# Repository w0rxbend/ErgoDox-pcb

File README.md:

# ErgoDox RP2040

An ErgoDox split keyboard PCB rebuilt around an RP2040 in each half, with ZMK firmware, USB-C on every port and one RGB LED per key. It keeps the original ErgoDox switch positions, so it fits the Litster acrylic case.

**Status: in development. The boards are not finished and have never been fabricated. Do not order them yet.** See [PLAN.md](PLAN.md) for what is open.

Project page: <https://w0rxbend.github.io/ErgoDox-pcb/>

Front, left and right half. The switches plug in from this side. The small squares are the LED cutouts.

Back, seen from behind, so the right half is on the left. Sockets, diodes, LEDs and the controller are all here.

These are KiCad 3D renders of the current placement. The signal tracks are not routed yet, and the USB-C receptacles and buttons have no 3D model, so only their pads show on the front.

## What it is

| | Original ErgoDox (2016) | ErgoDox RP2040 |
| --- | --- | --- |
| Controller | Teensy 2.0 plus MCP23018 expander | One RP2040 per half |
| Firmware | QMK and others | ZMK, wired split |
| Computer port | Mini-USB | USB-C |
| Link between halves | TRRS, I2C | USB-C cable carrying UART |
| Master half | Fixed (the Teensy side) | Either half |
| Switches | Soldered | Hotswap sockets |
| Lighting | 3 indicator LEDs | One SK6812MINI-E per key |
| Board | One reversible 2-layer PCB | Separate left and right 4-layer PCBs |
| Keys | 38 per half | 38 per half |

### Either half can be the master

Both halves carry the same circuit. ZMK fixes the role at build time, so there are four firmware images: left or right, central or peripheral. Flash the central image into the half you plug into the computer and the peripheral image into the other half. To swap sides, reflash both halves over USB.

The link port is a USB-C receptacle, but it carries UART and 5 V, not USB. It is marked `LINK` and `NOT A PC PORT` on the board.

## Repository layout

| Path | Contents |
| --- | --- |
| `hw/ergodox-rp2040/DESIGN.md` | The design contract: circuit, pin map, parts, acceptance checks |
| `hw/ergodox-rp2040/left`, `right` | Generated KiCad 10 projects |
| `hw/ergodox-rp2040/tools` | Python scripts that generate the schematics and boards |
| `hw/ergodox-rp2040/firmware/zmk` | ZMK shield, as a Zephyr module |
| `hw/ergodox-rp2040/notes` | Geometry taken from the legacy board, part research, ZMK notes |
| `hw/ergodox-rp2040/third_party/MX_V2` | ai03 keyswitch footprint library |
| `docs` | Source of the project page |
| `ErgoDOX pcb` | The original 2016 KiCad board. Kept unchanged for reference |
| `ErgoDox Acrylic Case` | Litster acrylic case drawings. Kept unchanged |

## Rebuild the boards

The KiCad files are generated. Do not edit them by hand; change the scripts and run them again.

You need Docker and the `kicad/kicad:10.0.7-full` image.

From the repository root:

```sh
hw/ergodox-rp2040/tools/build.sh
```

The script runs these steps for both halves:

1. `build_board.py` writes the schematics and places every part.
2. `kicad-cli pcb drc` lists the open connections.
3. `finish.py` routes them. It is a grid router written for this board: 0.1 mm signal tracks, 0.4 mm power tracks and 0.2907 mm USB tracks, on the outer layers and on In2 round the controller. This takes one to three hours per half.
4. `kicad-cli pcb drc` fills the zones and writes the reports to `hw/ergodox-rp2040/reports`.

Write the JLCPCB files (Gerber zip, BOM and CPL) to `hw/ergodox-rp2040/fab` with:

```sh
hw/ergodox-rp2040/tools/export_fab.sh
```

Render the boards again after a change:

```sh
docker run --rm --user "$(id -u):$(id -g)" -e HOME=/tmp -v "$PWD":/work -w /work/hw/ergodox-rp2040 \
  kicad/kicad:10.0.7-full kicad-cli pcb render --side top --background transparent \
  -o /work/right-front.png right/ergodox-rp2040-right.kicad_pcb
```

Use `--side bottom` for the back. The README images are the left and right renders joined side by side.

Check the firmware pin map against the schematics with:

```sh
python3 hw/ergodox-rp2040/tools/check_firmware_pins.py
```

## Firmware

The ZMK shield is in `hw/ergodox-rp2040/firmware/zmk`. Add that directory to your ZMK build as an extra module and build these shields for the `rpi_pico` board:

- `ergodox_rp2040_left_central`
- `ergodox_rp2040_left_peripheral`
- `ergodox_rp2040_right_central`
- `ergodox_rp2040_right_peripheral`

The firmware has not been built or run on hardware yet. LED brightness is capped at 10% so both halves stay within 500 mA from one USB port.

## Known limits

- ZMK's wired split is new and has no runtime role switch. The role follows the flashed image.
- The RP2040 drives the LED data line at 3.3 V with no level shifter. This is outside the LED's guaranteed input level at 5 V.
- The USB-C openings have not been test fitted in the Litster case.
- Some resistor values have no verified JLCPCB part number yet. `DESIGN.md` lists them.

## Credits

Based on the open [ErgoDox](https://github.com/Ergodox-io/ErgoDox) PCB and the acrylic case designed by Litster. Keyswitch footprints are from ai03's MX_V2 library.

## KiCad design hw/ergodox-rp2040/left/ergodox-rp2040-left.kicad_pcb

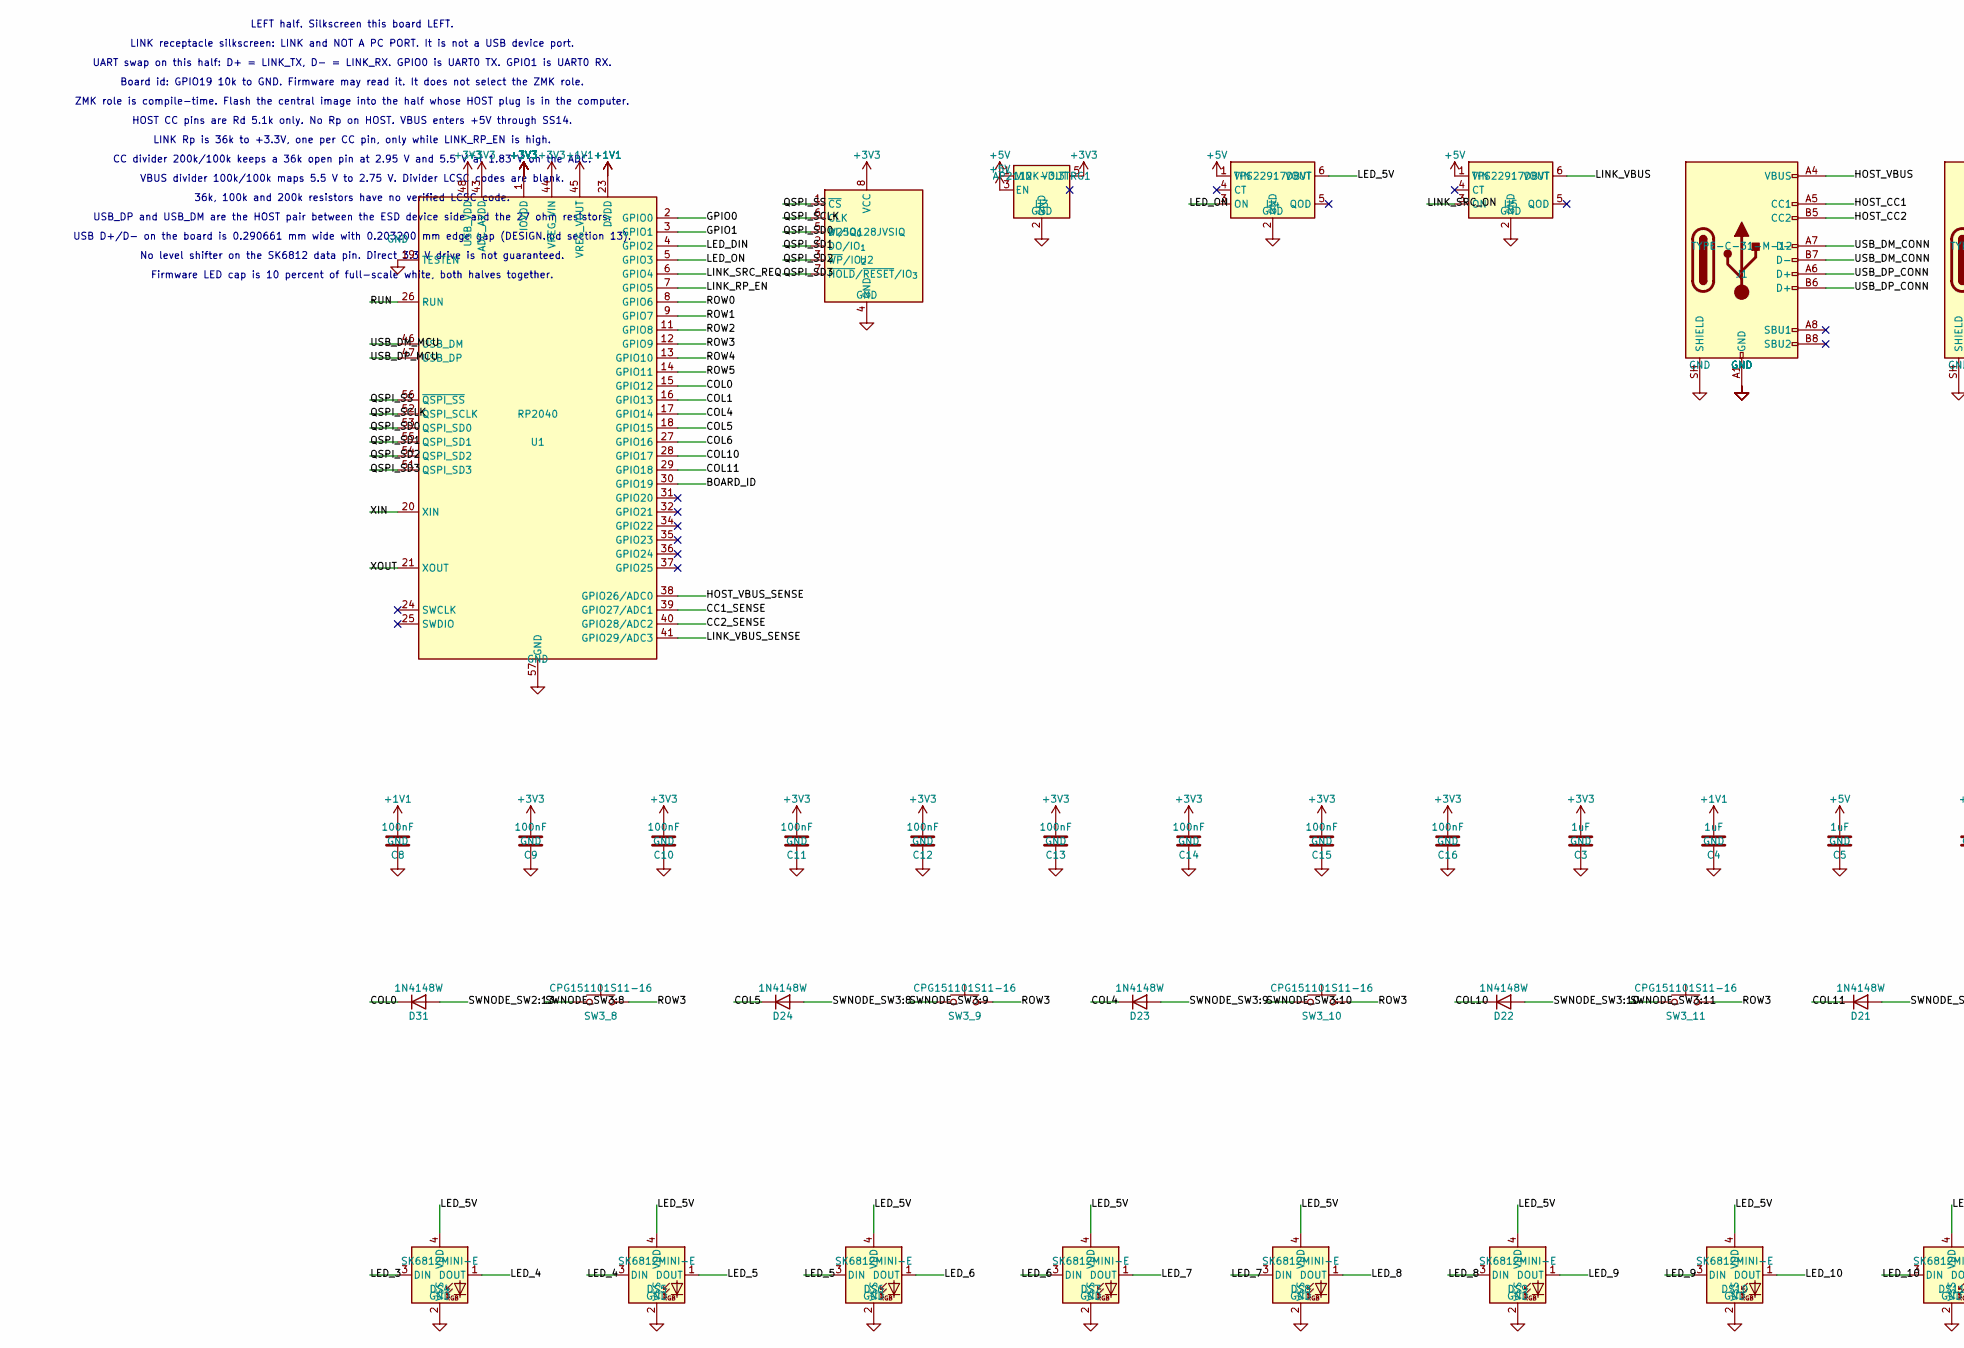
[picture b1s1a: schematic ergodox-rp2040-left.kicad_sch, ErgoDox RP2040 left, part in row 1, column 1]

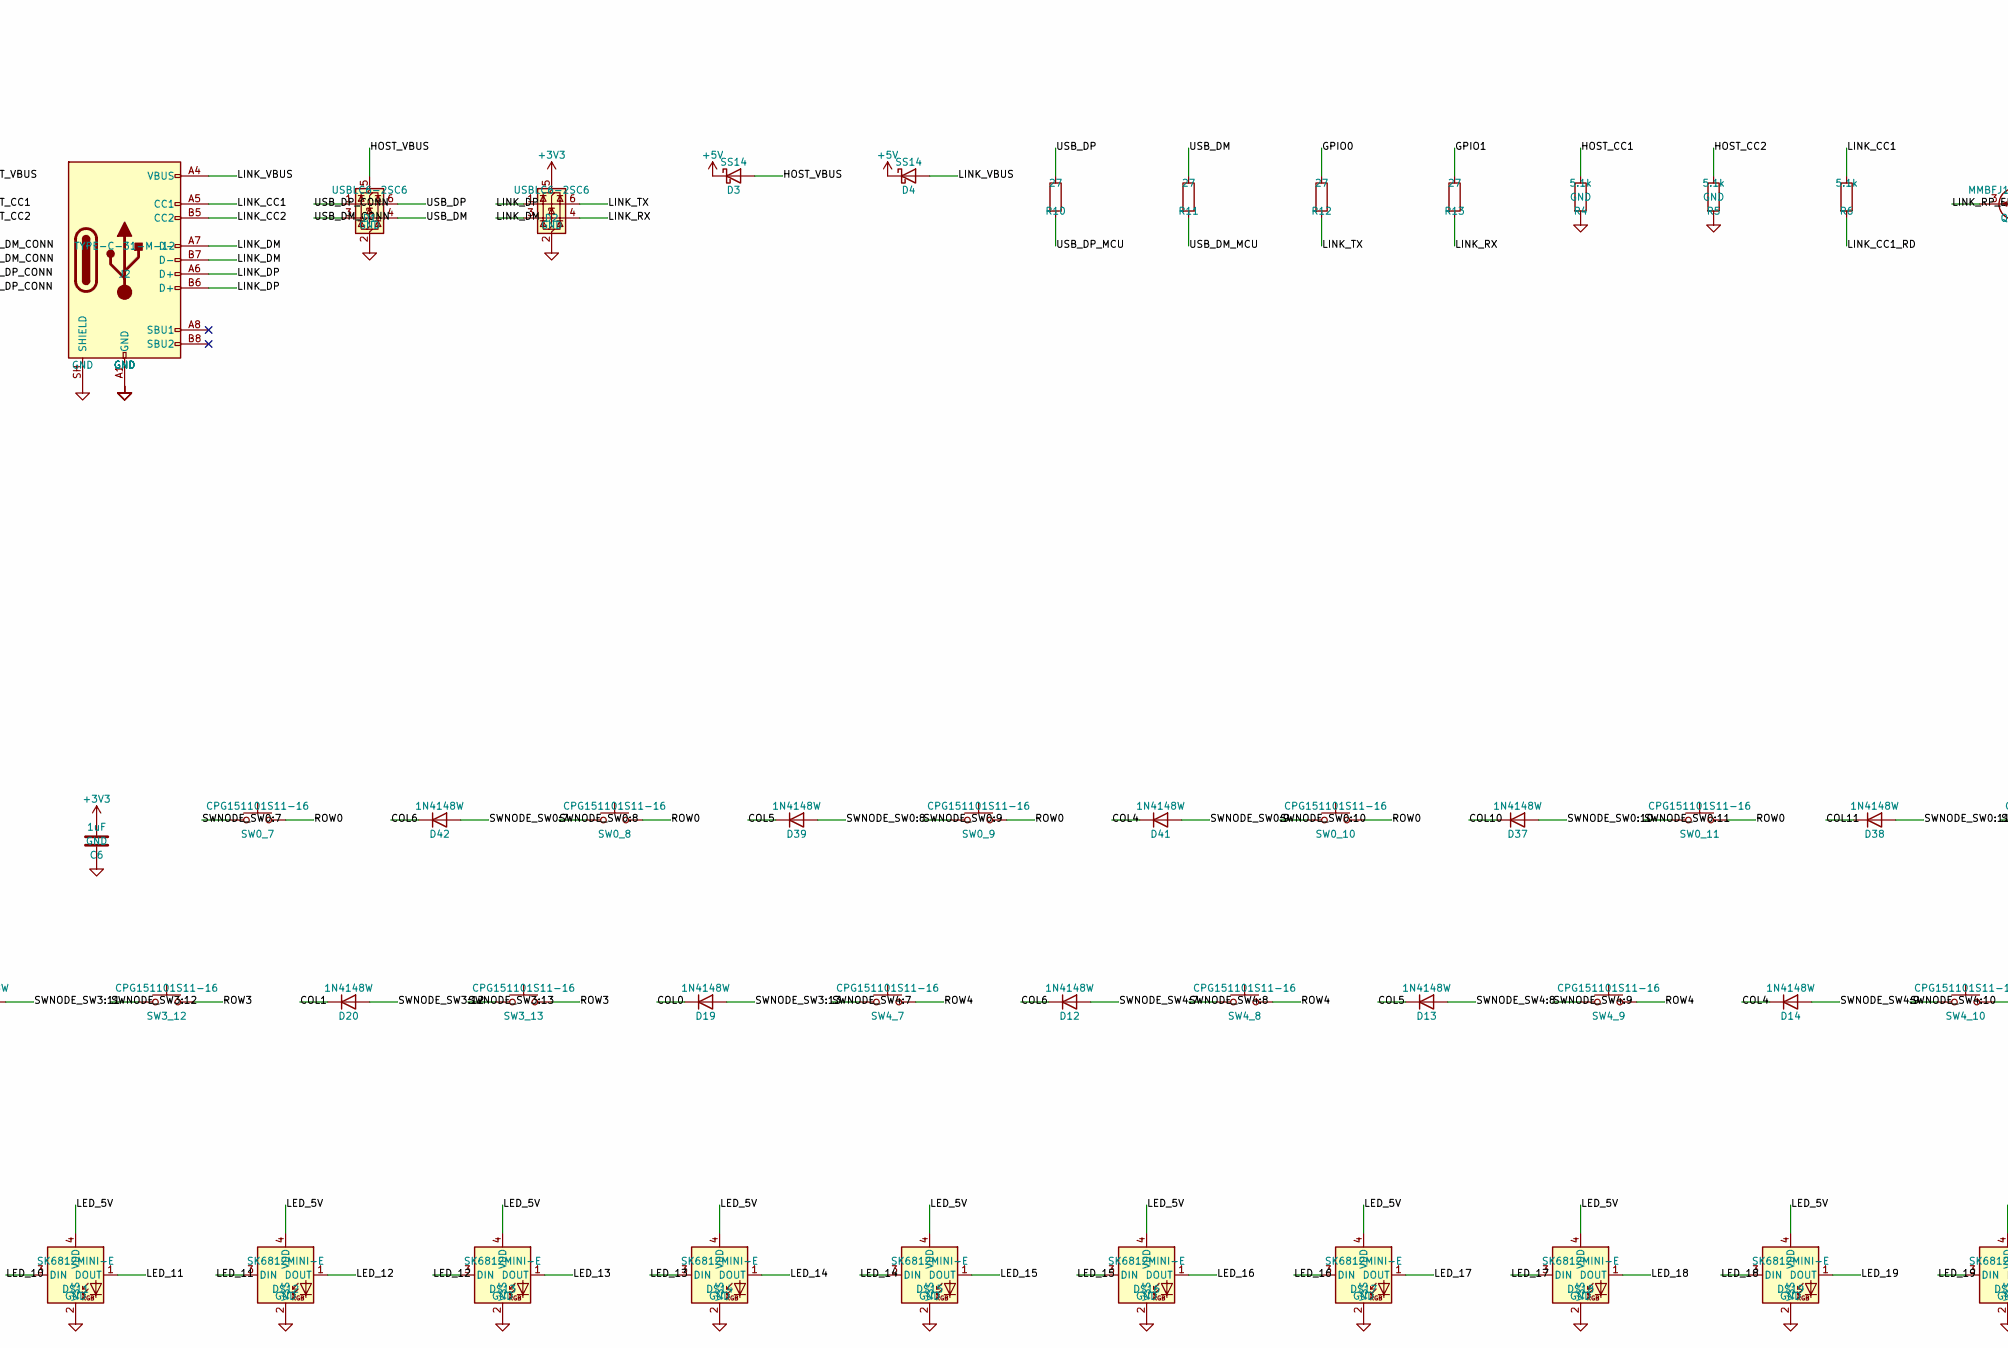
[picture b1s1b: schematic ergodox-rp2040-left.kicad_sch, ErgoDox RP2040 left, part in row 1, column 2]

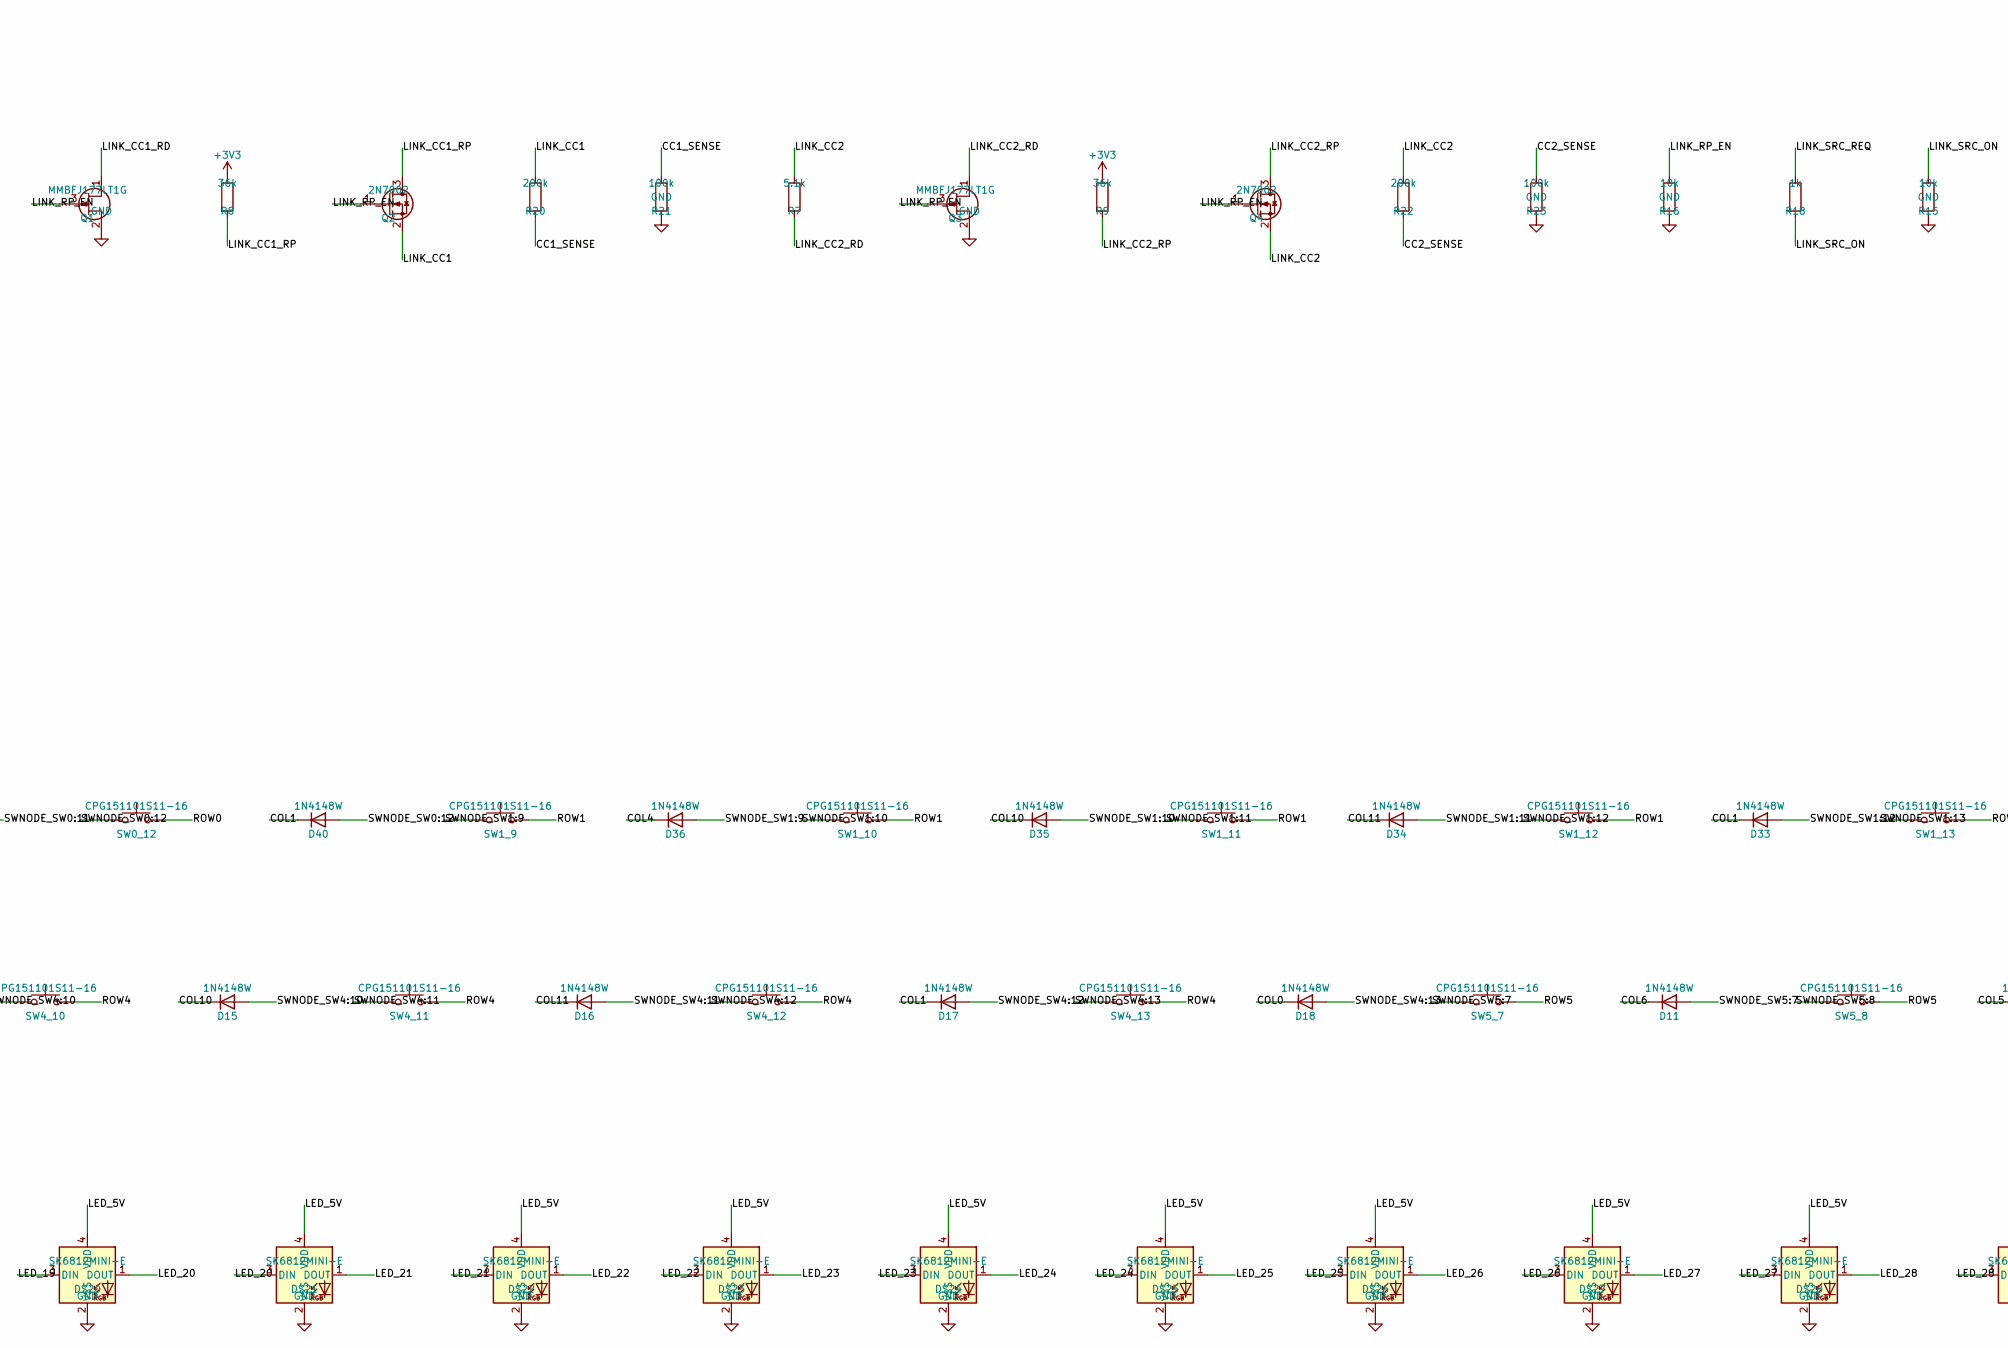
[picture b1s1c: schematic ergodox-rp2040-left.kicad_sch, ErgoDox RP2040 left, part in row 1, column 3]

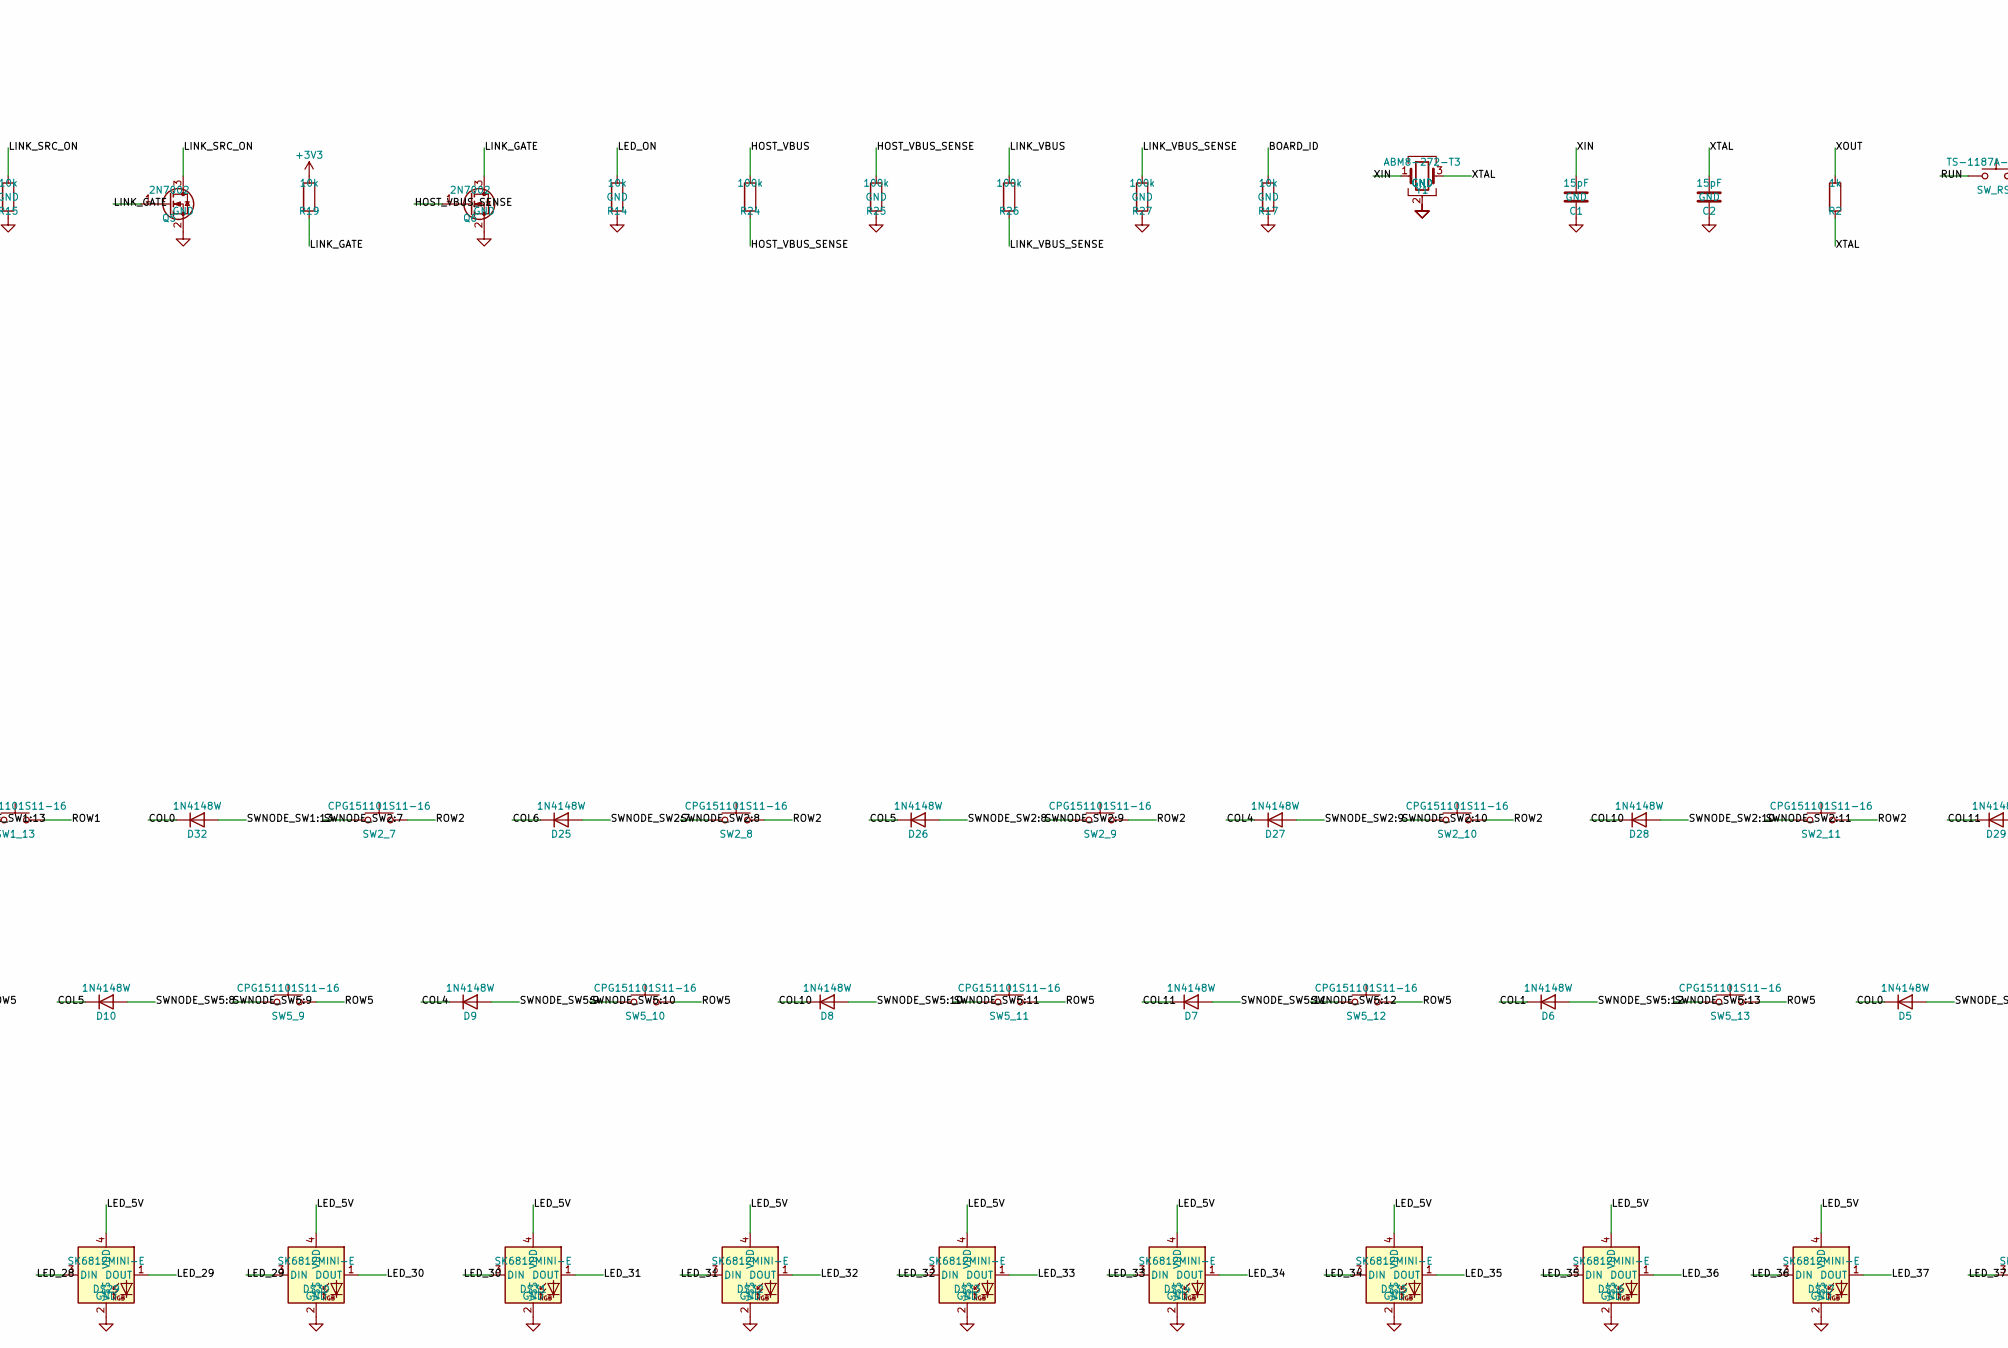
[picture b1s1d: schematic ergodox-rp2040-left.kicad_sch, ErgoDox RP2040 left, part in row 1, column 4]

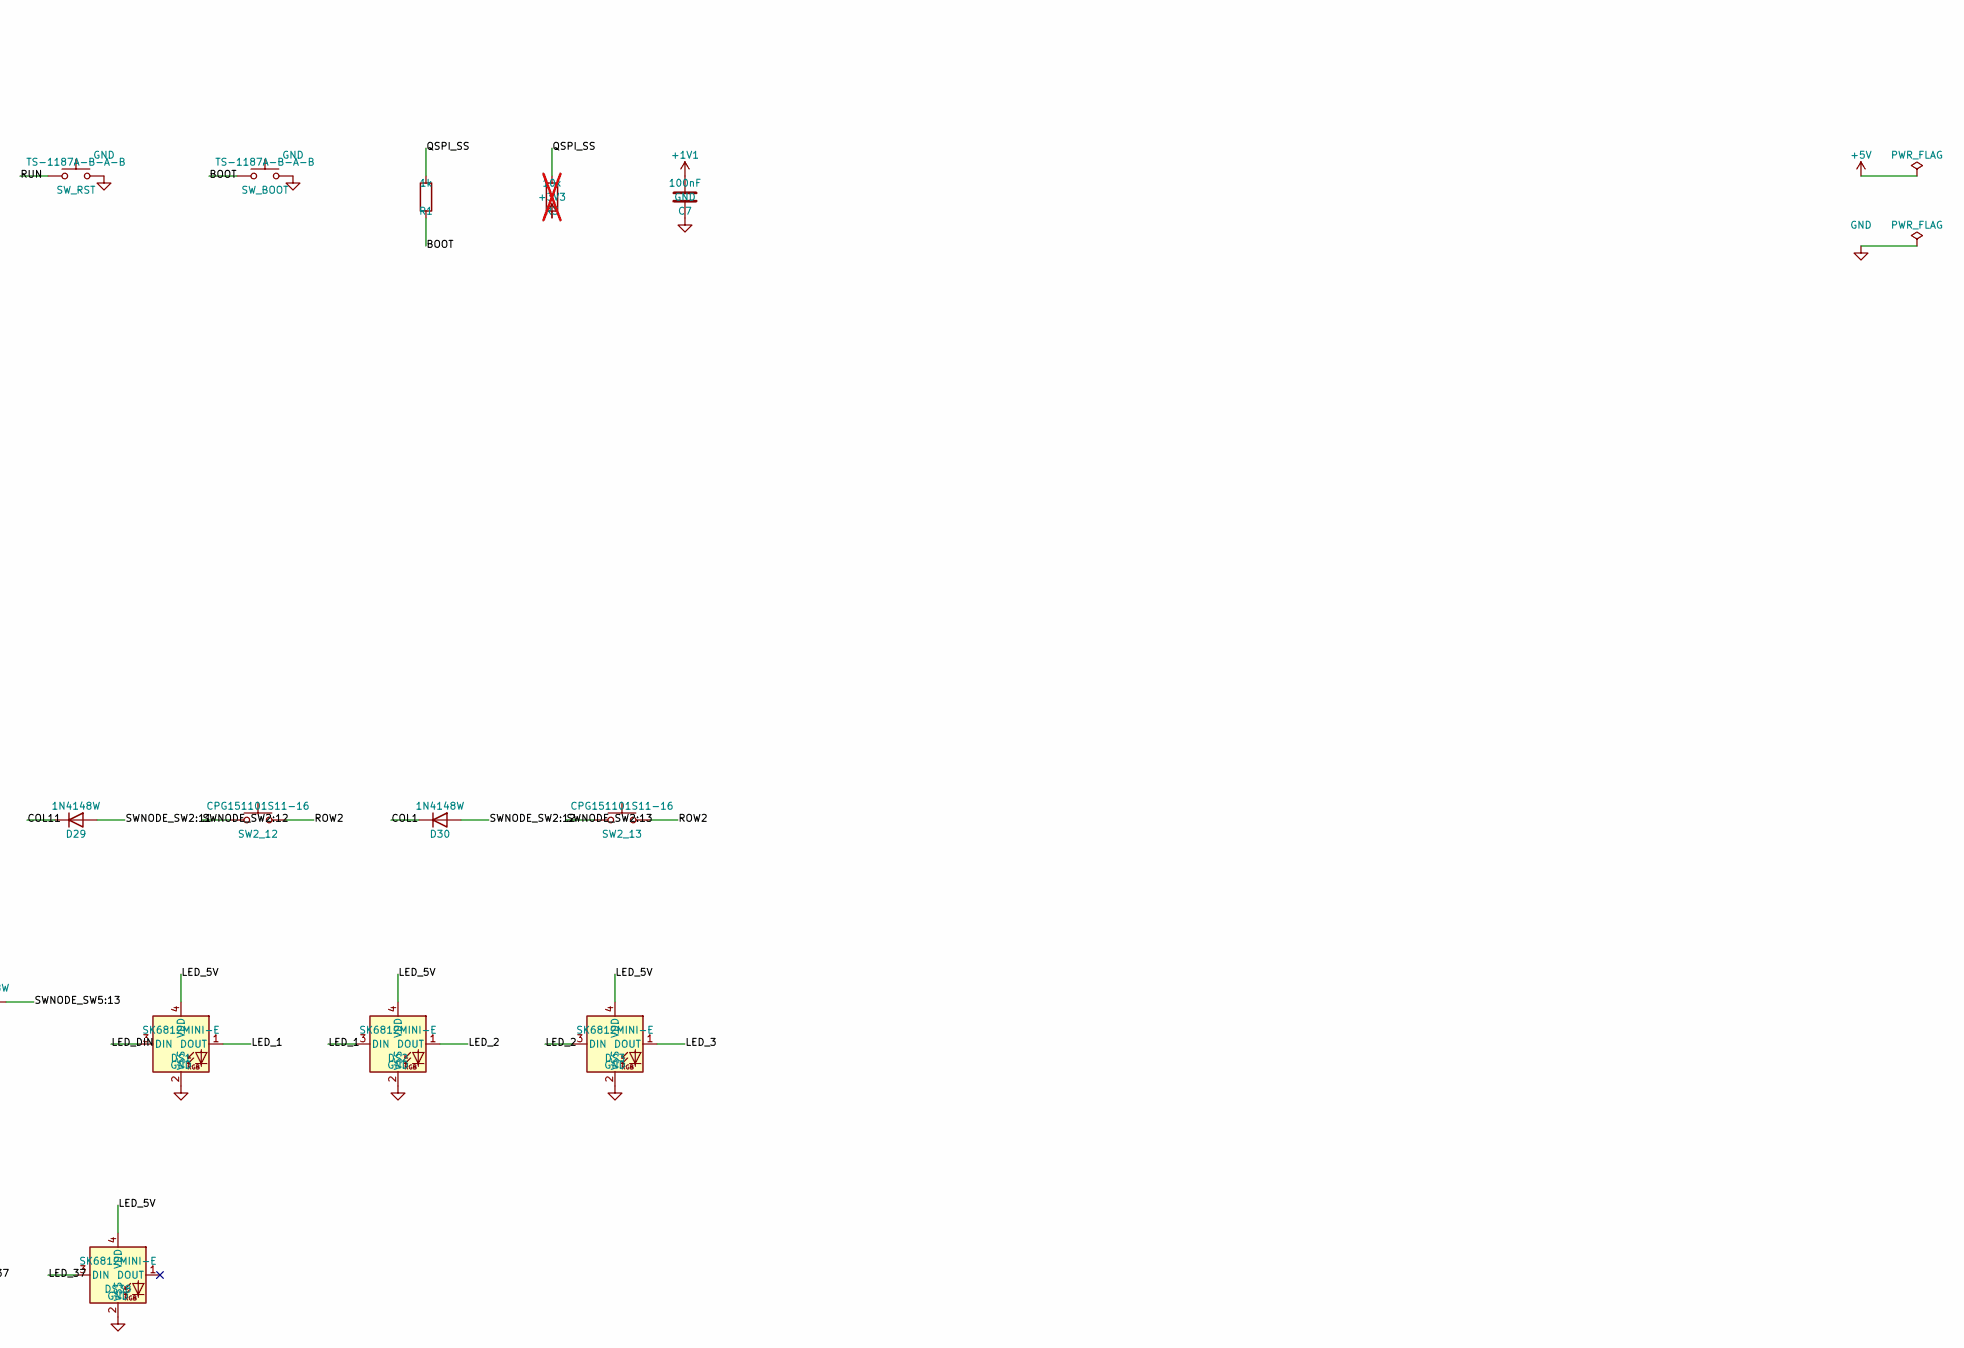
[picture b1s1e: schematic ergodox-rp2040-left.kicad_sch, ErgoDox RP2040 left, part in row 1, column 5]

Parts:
C1, C2: 15pF; C_0402_1005Metric; LCSC C1548
C3, C4, C5, C6: 1uF; C_0402_1005Metric; LCSC C52923
C7, C8, C9, C10, C11, C12, C13, C14, C15, C16: 100nF; C_0402_1005Metric; LCSC C1525
D1, D2: USBLC6-2SC6; SOT-23-6; MPN USBLC6-2SC6; LCSC C7519
D3, D4: SS14; D_SMA; MPN SS14; LCSC C2480
D5, D6, D7, D8, D9, D10, D11, D12, D13, D14, D15, D16, D17, D18, D19, D20, D21, D22, D23, D24, D25, D26, D27, D28, D29, D30, D31, D32, D33, D34, D35, D36, D37, D38, D39, D40, D41, D42: 1N4148W; D_SOD-123; MPN 1N4148W; LCSC C81598
DS1, DS2, DS3, DS4, DS5, DS6, DS7, DS8, DS9, DS10, DS11, DS12, DS13, DS14, DS15, DS16, DS17, DS18, DS19, DS20, DS21, DS22, DS23, DS24, DS25, DS26, DS27, DS28, DS29, DS30, DS31, DS32, DS33, DS34, DS35, DS36, DS37, DS38: SK6812MINI-E; LED_SK6812MINI-E_3.2x2.8mm_P1.5mm_ReverseMount; MPN SK6812MINI-E; LCSC C5149201
J1, J2: TYPE-C-31-M-12; USB_C_Receptacle_HRO_TYPE-C-31-M-12; MPN TYPE-C-31-M-12; LCSC C165948
Q1, Q3: MMBFJ177LT1G; SOT-23; MPN MMBFJ177LT1G; LCSC C106763
Q2, Q4, Q5, Q6: 2N7002; SOT-23; MPN 2N7002; LCSC C8545
R1, R2, R18: 1k; R_0402_1005Metric; LCSC C11702
R3: 10k; R_0402_1005Metric; LCSC C25744; not fitted
R4, R5, R6, R7: 5.1k; R_0402_1005Metric; LCSC C25905
R8, R9: 36k; R_0402_1005Metric
R10, R11, R12, R13: 27; R_0402_1005Metric; LCSC C25100
R14, R15, R16, R17, R19: 10k; R_0402_1005Metric; LCSC C25744
R20, R22: 200k; R_0402_1005Metric
R21, R23, R24, R25, R26, R27: 100k; R_0402_1005Metric
SW0_7, SW0_8, SW0_9, SW0_10, SW0_11, SW0_12, SW1_9, SW1_10, SW1_11, SW1_12, SW1_13, SW2_7, SW2_8, SW2_9, SW2_10, SW2_11, SW2_12, SW2_13, SW3_8, SW3_9, SW3_10, SW3_11, SW3_12, SW3_13, SW4_7, SW4_8, SW4_9, SW4_10, SW4_11, SW4_12, SW4_13, SW5_7, SW5_8, SW5_9, SW5_10, SW5_11, SW5_12, SW5_13: CPG151101S11-16; MX-Hotswap-1U; MPN CPG151101S11-16; LCSC C41430893
SW_BOOT: TS-1187A-B-A-B; SW_Push_1P1T_XKB_TS-1187A; LCSC C318884
SW_RST: TS-1187A-B-A-B; SW_Push_1P1T_XKB_TS-1187A; LCSC C318884
U1: RP2040; QFN-56-1EP_7x7mm_P0.4mm_EP3.2x3.2mm_ThermalVias; MPN RP2040; LCSC C2040
U2: W25Q128JVSIQ; SOIC-8_5.3x5.3mm_P1.27mm; MPN W25Q128JVSIQ; LCSC C97521
U3: AP2112K-3.3TRG1; SOT-23-5; MPN AP2112K-3.3TRG1; LCSC C51118
U4, U5: TPS22917DBVT; SOT-23-6; MPN TPS22917DBVT; LCSC C2680344
Y1: ABM8-272-T3; Crystal_SMD_3225-4Pin_3.2x2.5mm; MPN ABM8-272-T3; LCSC C20625731

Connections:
+1V1: C4.1, C7.1, C8.1, U1.23 (DVDD), U1.45 (VREG_VOUT), U1.50 (DVDD)
+3V3: C3.1, C6.1, C9.1, C10.1, C11.1, C12.1, C13.1, C14.1, C15.1, C16.1, D2.5 (VBUS), R3.2, R8.1, R9.1, R19.1, U1.1 (IOVDD), U1.10 (IOVDD), U1.22 (IOVDD), U1.33 (IOVDD), U1.42 (IOVDD), U1.43 (ADC_AVDD), U1.44 (VREG_VIN), U1.48 (USB_VDD), U1.49 (IOVDD), U2.8 (VCC), U3.5 (VOUT)
+5V: C5.1, D3.1 (K), D4.1 (K), U3.1 (VIN), U3.3 (EN), U4.1 (VIN), U5.1 (VIN)
BOARD_ID: R17.1, U1.30 (GPIO19)
BOOT: R1.2, SW_BOOT.1
CC1_SENSE: R20.2, R21.1, U1.39 (GPIO27/ADC1)
CC2_SENSE: R22.2, R23.1, U1.40 (GPIO28/ADC2)
COL0: D5.1 (K), D18.1 (K), D19.1 (K), D31.1 (K), D32.1 (K), U1.15 (GPIO12)
COL1: D6.1 (K), D17.1 (K), D20.1 (K), D30.1 (K), D33.1 (K), D40.1 (K), U1.16 (GPIO13)
COL4: D9.1 (K), D14.1 (K), D23.1 (K), D27.1 (K), D36.1 (K), D41.1 (K), U1.17 (GPIO14)
COL5: D10.1 (K), D13.1 (K), D24.1 (K), D26.1 (K), D39.1 (K), U1.18 (GPIO15)
COL6: D11.1 (K), D12.1 (K), D25.1 (K), D42.1 (K), U1.27 (GPIO16)
COL10: D8.1 (K), D15.1 (K), D22.1 (K), D28.1 (K), D35.1 (K), D37.1 (K), U1.28 (GPIO17)
COL11: D7.1 (K), D16.1 (K), D21.1 (K), D29.1 (K), D34.1 (K), D38.1 (K), U1.29 (GPIO18)
GND: C1.2, C2.2, C3.2, C4.2, C5.2, C6.2, C7.2, C8.2, C9.2, C10.2, C11.2, C12.2, C13.2, C14.2, C15.2, C16.2, D1.2 (GND), D2.2 (GND), DS1.2 (VSS), DS2.2 (VSS), DS3.2 (VSS), DS4.2 (VSS), DS5.2 (VSS), DS6.2 (VSS), DS7.2 (VSS), DS8.2 (VSS), DS9.2 (VSS), DS10.2 (VSS), DS11.2 (VSS), DS12.2 (VSS), DS13.2 (VSS), DS14.2 (VSS), DS15.2 (VSS), DS16.2 (VSS), DS17.2 (VSS), DS18.2 (VSS), DS19.2 (VSS), DS20.2 (VSS), DS21.2 (VSS), DS22.2 (VSS), DS23.2 (VSS), DS24.2 (VSS), DS25.2 (VSS), DS26.2 (VSS), DS27.2 (VSS), DS28.2 (VSS), DS29.2 (VSS), DS30.2 (VSS), DS31.2 (VSS), DS32.2 (VSS), DS33.2 (VSS), DS34.2 (VSS), DS35.2 (VSS), DS36.2 (VSS), DS37.2 (VSS), DS38.2 (VSS), J1.A1 (GND), J1.A12 (GND), J1.B1 (GND), J1.B12 (GND), J1.SH (SHIELD), J2.A1 (GND), J2.A12 (GND), J2.B1 (GND), J2.B12 (GND), J2.SH (SHIELD), Q1.2 (S), Q3.2 (S), Q5.2 (S), Q6.2 (S), R4.2, R5.2, R14.2, R15.2, R16.2, R17.2, R21.2, R23.2, R25.2, R27.2, SW_BOOT.2, SW_RST.2, U1.19 (TESTEN), U1.57 (GND), U2.4 (GND), U3.2 (GND), U4.2 (GND), U5.2 (GND), Y1.2 (G), Y1.4 (G)
GPIO0: R12.1, U1.2 (GPIO0)
GPIO1: R13.1, U1.3 (GPIO1)
HOST_CC1: J1.A5 (CC1), R4.1
HOST_CC2: J1.B5 (CC2), R5.1
HOST_VBUS: D1.5 (VBUS), D3.2 (A), J1.A4 (VBUS), J1.A9 (VBUS), J1.B4 (VBUS), J1.B9 (VBUS), R24.1
HOST_VBUS_SENSE: Q6.1 (G), R24.2, R25.1, U1.38 (GPIO26/ADC0)
LED_1: DS1.1 (DOUT), DS2.3 (DIN)
LED_2: DS2.1 (DOUT), DS3.3 (DIN)
LED_3: DS3.1 (DOUT), DS4.3 (DIN)
LED_4: DS4.1 (DOUT), DS5.3 (DIN)
LED_5: DS5.1 (DOUT), DS6.3 (DIN)
LED_5V: DS1.4 (VDD), DS2.4 (VDD), DS3.4 (VDD), DS4.4 (VDD), DS5.4 (VDD), DS6.4 (VDD), DS7.4 (VDD), DS8.4 (VDD), DS9.4 (VDD), DS10.4 (VDD), DS11.4 (VDD), DS12.4 (VDD), DS13.4 (VDD), DS14.4 (VDD), DS15.4 (VDD), DS16.4 (VDD), DS17.4 (VDD), DS18.4 (VDD), DS19.4 (VDD), DS20.4 (VDD), DS21.4 (VDD), DS22.4 (VDD), DS23.4 (VDD), DS24.4 (VDD), DS25.4 (VDD), DS26.4 (VDD), DS27.4 (VDD), DS28.4 (VDD), DS29.4 (VDD), DS30.4 (VDD), DS31.4 (VDD), DS32.4 (VDD), DS33.4 (VDD), DS34.4 (VDD), DS35.4 (VDD), DS36.4 (VDD), DS37.4 (VDD), DS38.4 (VDD), U4.6 (VOUT)
LED_6: DS6.1 (DOUT), DS7.3 (DIN)
LED_7: DS7.1 (DOUT), DS8.3 (DIN)
LED_8: DS8.1 (DOUT), DS9.3 (DIN)
LED_9: DS9.1 (DOUT), DS10.3 (DIN)
LED_10: DS10.1 (DOUT), DS11.3 (DIN)
LED_11: DS11.1 (DOUT), DS12.3 (DIN)
LED_12: DS12.1 (DOUT), DS13.3 (DIN)
LED_13: DS13.1 (DOUT), DS14.3 (DIN)
LED_14: DS14.1 (DOUT), DS15.3 (DIN)
LED_15: DS15.1 (DOUT), DS16.3 (DIN)
LED_16: DS16.1 (DOUT), DS17.3 (DIN)
LED_17: DS17.1 (DOUT), DS18.3 (DIN)
LED_18: DS18.1 (DOUT), DS19.3 (DIN)
LED_19: DS19.1 (DOUT), DS20.3 (DIN)
LED_20: DS20.1 (DOUT), DS21.3 (DIN)
LED_21: DS21.1 (DOUT), DS22.3 (DIN)
LED_22: DS22.1 (DOUT), DS23.3 (DIN)
LED_23: DS23.1 (DOUT), DS24.3 (DIN)
LED_24: DS24.1 (DOUT), DS25.3 (DIN)
LED_25: DS25.1 (DOUT), DS26.3 (DIN)
LED_26: DS26.1 (DOUT), DS27.3 (DIN)
LED_27: DS27.1 (DOUT), DS28.3 (DIN)
LED_28: DS28.1 (DOUT), DS29.3 (DIN)
LED_29: DS29.1 (DOUT), DS30.3 (DIN)
LED_30: DS30.1 (DOUT), DS31.3 (DIN)
LED_31: DS31.1 (DOUT), DS32.3 (DIN)
LED_32: DS32.1 (DOUT), DS33.3 (DIN)
LED_33: DS33.1 (DOUT), DS34.3 (DIN)
LED_34: DS34.1 (DOUT), DS35.3 (DIN)
LED_35: DS35.1 (DOUT), DS36.3 (DIN)
LED_36: DS36.1 (DOUT), DS37.3 (DIN)
LED_37: DS37.1 (DOUT), DS38.3 (DIN)
LED_DIN: DS1.3 (DIN), U1.4 (GPIO2)
LED_ON: R14.1, U1.5 (GPIO3), U4.3 (ON)
LINK_CC1: J2.A5 (CC1), Q2.2 (S), R6.1, R20.1
LINK_CC1_RD: Q1.1 (D), R6.2
LINK_CC1_RP: Q2.3 (D), R8.2
LINK_CC2: J2.B5 (CC2), Q4.2 (S), R7.1, R22.1
LINK_CC2_RD: Q3.1 (D), R7.2
LINK_CC2_RP: Q4.3 (D), R9.2
LINK_DM: D2.3 (I/O2), J2.A7 (D-), J2.B7 (D-)
LINK_DP: D2.1 (I/O1), J2.A6 (D+), J2.B6 (D+)
LINK_GATE: Q5.1 (G), Q6.3 (D), R19.2
LINK_RP_EN: Q1.3 (G), Q2.1 (G), Q3.3 (G), Q4.1 (G), R16.1, U1.7 (GPIO5)
LINK_RX: D2.4 (I/O2), R13.2
LINK_SRC_ON: Q5.3 (D), R15.1, R18.2, U5.3 (ON)
LINK_SRC_REQ: R18.1, U1.6 (GPIO4)
LINK_TX: D2.6 (I/O1), R12.2
LINK_VBUS: D4.2 (A), J2.A4 (VBUS), J2.A9 (VBUS), J2.B4 (VBUS), J2.B9 (VBUS), R26.1, U5.6 (VOUT)
LINK_VBUS_SENSE: R26.2, R27.1, U1.41 (GPIO29/ADC3)
QSPI_SCLK: U1.52 (QSPI_SCLK), U2.6 (CLK)
QSPI_SD0: U1.53 (QSPI_SD0), U2.5 (DI/IO_{0})
QSPI_SD1: U1.55 (QSPI_SD1), U2.2 (DO/IO_{1})
QSPI_SD2: U1.54 (QSPI_SD2), U2.3 (~WP/IO_{2})
QSPI_SD3: U1.51 (QSPI_SD3), U2.7 (~HOLD/~RESET/IO_{3})
QSPI_SS: R1.1, R3.1, U1.56 (~QSPI_SS), U2.1 (~CS)
ROW0: SW0_7.2, SW0_8.2, SW0_9.2, SW0_10.2, SW0_11.2, SW0_12.2, U1.8 (GPIO6)
ROW1: SW1_9.2, SW1_10.2, SW1_11.2, SW1_12.2, SW1_13.2, U1.9 (GPIO7)
ROW2: SW2_7.2, SW2_8.2, SW2_9.2, SW2_10.2, SW2_11.2, SW2_12.2, SW2_13.2, U1.11 (GPIO8)
ROW3: SW3_8.2, SW3_9.2, SW3_10.2, SW3_11.2, SW3_12.2, SW3_13.2, U1.12 (GPIO9)
ROW4: SW4_7.2, SW4_8.2, SW4_9.2, SW4_10.2, SW4_11.2, SW4_12.2, SW4_13.2, U1.13 (GPIO10)
ROW5: SW5_7.2, SW5_8.2, SW5_9.2, SW5_10.2, SW5_11.2, SW5_12.2, SW5_13.2, U1.14 (GPIO11)
RUN: SW_RST.1, U1.26 (RUN)
SWNODE_SW0:7: D42.2 (A), SW0_7.1
SWNODE_SW0:8: D39.2 (A), SW0_8.1
SWNODE_SW0:9: D41.2 (A), SW0_9.1
SWNODE_SW0:10: D37.2 (A), SW0_10.1
SWNODE_SW0:11: D38.2 (A), SW0_11.1
SWNODE_SW0:12: D40.2 (A), SW0_12.1
SWNODE_SW1:9: D36.2 (A), SW1_9.1
SWNODE_SW1:10: D35.2 (A), SW1_10.1
SWNODE_SW1:11: D34.2 (A), SW1_11.1
SWNODE_SW1:12: D33.2 (A), SW1_12.1
SWNODE_SW1:13: D32.2 (A), SW1_13.1
SWNODE_SW2:7: D25.2 (A), SW2_7.1
SWNODE_SW2:8: D26.2 (A), SW2_8.1
SWNODE_SW2:9: D27.2 (A), SW2_9.1
SWNODE_SW2:10: D28.2 (A), SW2_10.1
SWNODE_SW2:11: D29.2 (A), SW2_11.1
SWNODE_SW2:12: D30.2 (A), SW2_12.1
SWNODE_SW2:13: D31.2 (A), SW2_13.1
SWNODE_SW3:8: D24.2 (A), SW3_8.1
SWNODE_SW3:9: D23.2 (A), SW3_9.1
SWNODE_SW3:10: D22.2 (A), SW3_10.1
SWNODE_SW3:11: D21.2 (A), SW3_11.1
SWNODE_SW3:12: D20.2 (A), SW3_12.1
SWNODE_SW3:13: D19.2 (A), SW3_13.1
SWNODE_SW4:7: D12.2 (A), SW4_7.1
SWNODE_SW4:8: D13.2 (A), SW4_8.1
SWNODE_SW4:9: D14.2 (A), SW4_9.1
SWNODE_SW4:10: D15.2 (A), SW4_10.1
SWNODE_SW4:11: D16.2 (A), SW4_11.1
SWNODE_SW4:12: D17.2 (A), SW4_12.1
SWNODE_SW4:13: D18.2 (A), SW4_13.1
SWNODE_SW5:7: D11.2 (A), SW5_7.1
SWNODE_SW5:8: D10.2 (A), SW5_8.1
SWNODE_SW5:9: D9.2 (A), SW5_9.1
SWNODE_SW5:10: D8.2 (A), SW5_10.1
SWNODE_SW5:11: D7.2 (A), SW5_11.1
SWNODE_SW5:12: D6.2 (A), SW5_12.1
SWNODE_SW5:13: D5.2 (A), SW5_13.1
USB_DM: D1.4 (I/O2), R11.1
USB_DM_CONN: D1.3 (I/O2), J1.A7 (D-), J1.B7 (D-)
USB_DM_MCU: R11.2, U1.46 (USB_DM)
USB_DP: D1.6 (I/O1), R10.1
USB_DP_CONN: D1.1 (I/O1), J1.A6 (D+), J1.B6 (D+)
USB_DP_MCU: R10.2, U1.47 (USB_DP)
XIN: C1.1, U1.20 (XIN), Y1.1
XOUT: R2.1, U1.21 (XOUT)
XTAL: C2.1, R2.2, Y1.3

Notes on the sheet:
LEFT half. Silkscreen this board LEFT.
LINK receptacle silkscreen: LINK and NOT A PC PORT. It is not a USB device port.
UART swap on this half: D+ = LINK_TX, D- = LINK_RX. GPIO0 is UART0 TX. GPIO1 is UART0 RX.
Board id: GPIO19 10k to GND. Firmware may read it. It does not select the ZMK role.
ZMK role is compile-time. Flash the central image into the half whose HOST plug is in the computer.
HOST CC pins are Rd 5.1k only. No Rp on HOST. VBUS enters +5V through SS14.
LINK Rp is 36k to +3.3V, one per CC pin, only while LINK_RP_EN is high.
CC divider 200k/100k keeps a 36k open pin at 2.95 V and 5.5 V at 1.83 V on the ADC.
VBUS divider 100k/100k maps 5.5 V to 2.75 V. Divider LCSC codes are blank.
36k, 100k and 200k resistors have no verified LCSC code.
USB_DP and USB_DM are the HOST pair between the ESD device side and the 27 ohm resistors.
USB D+/D- on the board is 0.290661 mm wide with 0.203200 mm edge gap (DESIGN.md section 13).
No level shifter on the SK6812 data pin. Direct 3.3 V drive is not guaranteed.
Firmware LED cap is 10 percent of full-scale white, both halves together.

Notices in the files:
hw/ergodox-rp2040/tools/build_board.py:
LCSC codes copied from notes/parts.md and DESIGN.md, which cite the
JLCPCB part pages. Values with no code in those files stay blank.
